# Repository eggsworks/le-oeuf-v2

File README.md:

## L'oeuf

An ultra-low profile (Kailh PG1316S) keyboard inspired by Le Chiffre.

## PCB

L'oeuf is a semi-integrated PCB using an E73 BLE module. It is intended to be fully SMT assembled.

A mid-mount USB-C port and JST ACH battery connector keep the board as thin as possible.

## Firmware

ZMK firmware available from [eggsworks/zmk-config](https://github.com/eggsworks/zmk-config/)

## License

This design is available under the terms of the [CERN-OHL-S](LICENSE).

## Acknowledgements

- Inspired by the original [tominabox1/Le-Chiffre-Keyboard](https://github.com/tominabox1/Le-Chiffre-Keyboard/)
- E73 supporting circuitry derived from [krikun98/Willis](https://github.com/krikun98/Willis)
- MCU footprint derived from [ebastler/marbastlib](https://github.com/ebastler/marbastlib/)
- Switch footprint derived from [mikeholscher/zmk-config-mikefive](https://github.com/mikeholscher/zmk-config-mikefive/)
- Layout derived from ergogen source supplied for [sporkus/le_capybara_keyboard](https://github.com/sporkus/le_capybara_keyboard)
- PCB art kindly provided by transthropology

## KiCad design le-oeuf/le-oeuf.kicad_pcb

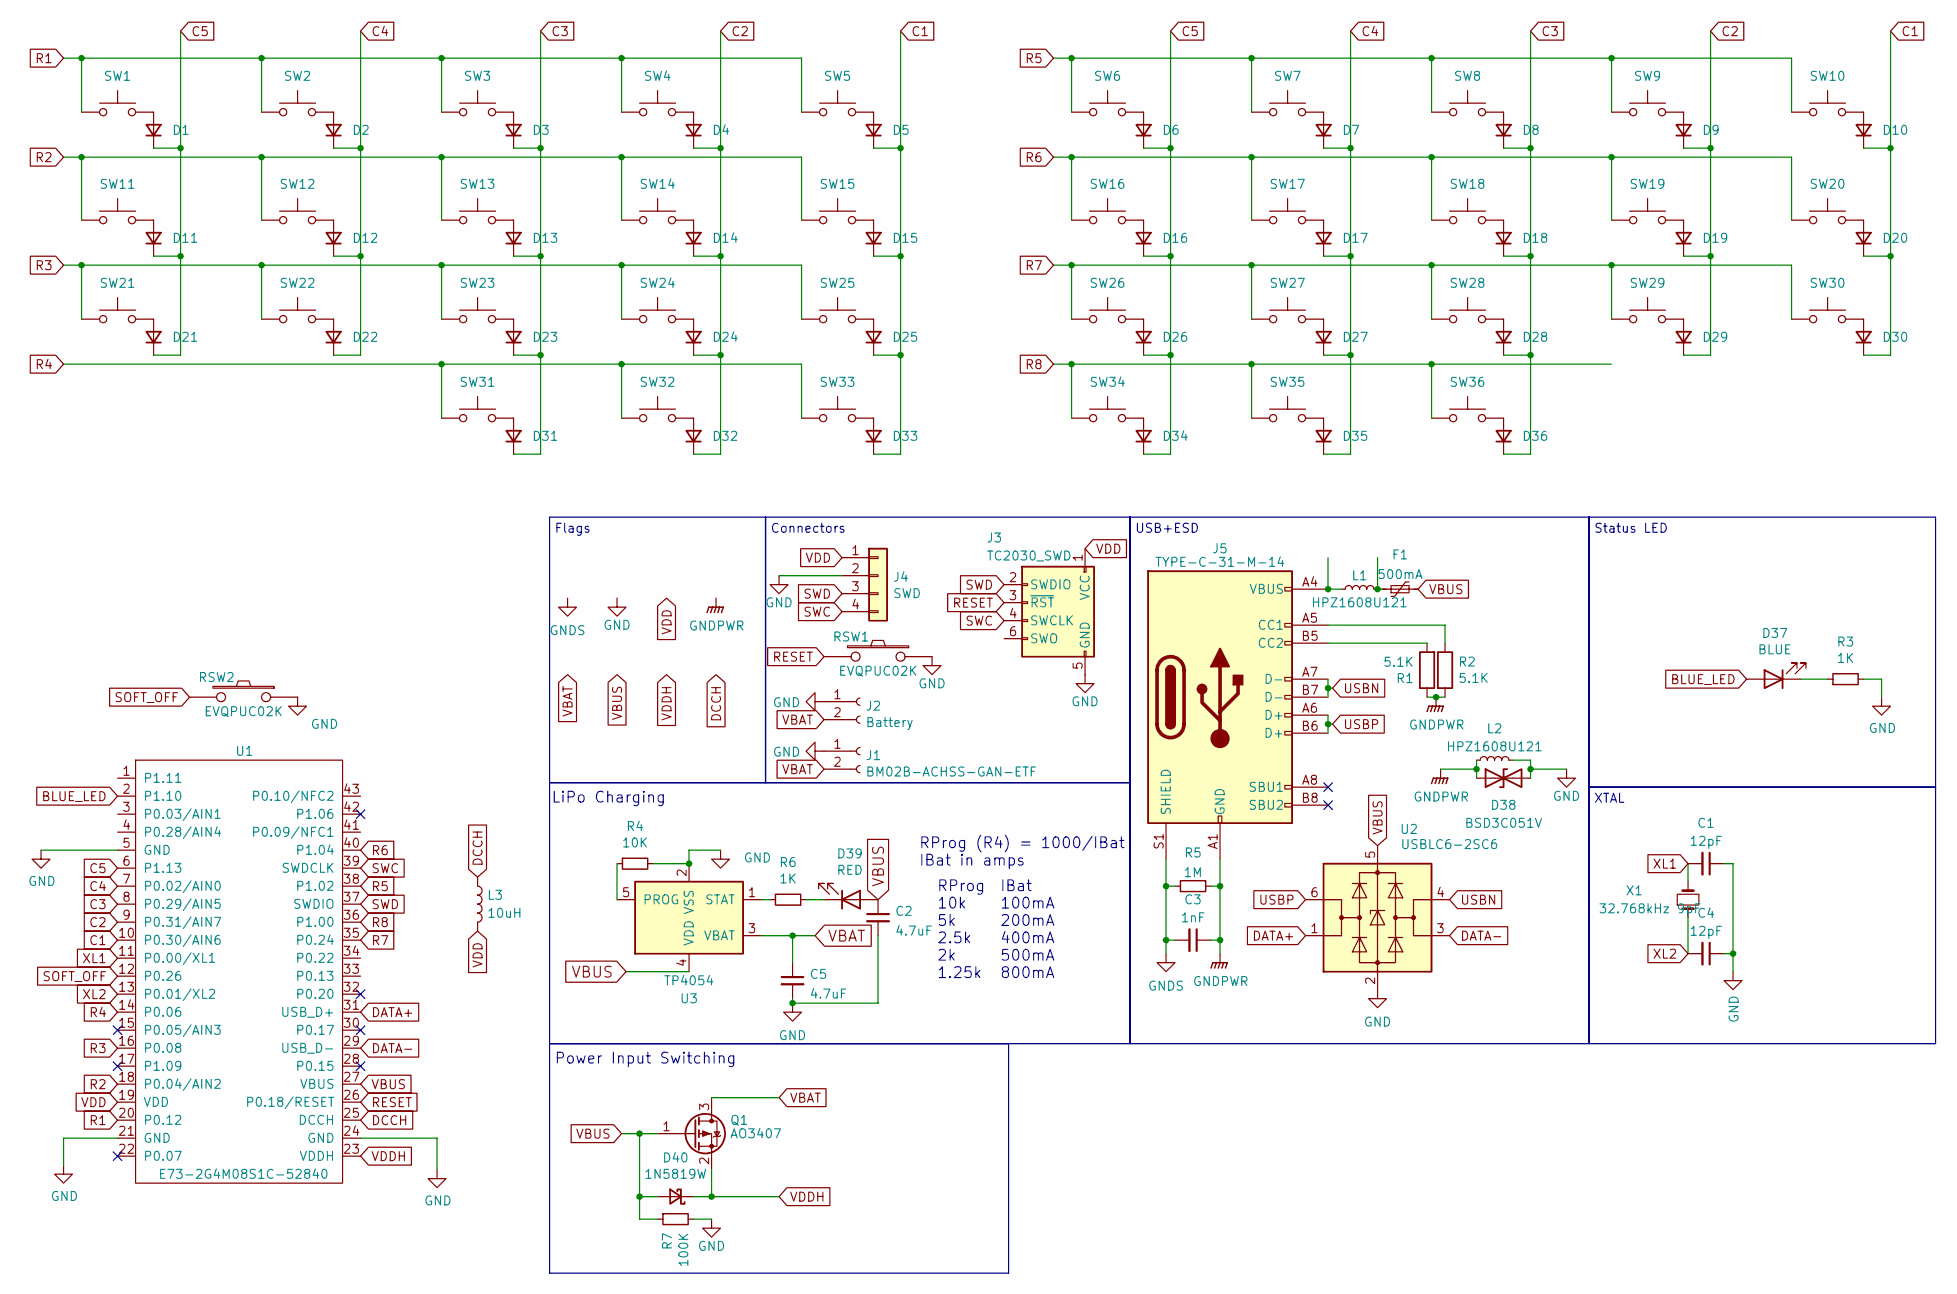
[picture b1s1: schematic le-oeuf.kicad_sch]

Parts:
C1, C4: 12pF; C_0603_1608Metric; MPN 0603CG120J500NT; LCSC C1642
C2, C5: 4.7uF; C_0603_1608Metric; MPN CL10A475KO8NNNC; LCSC C19666
C3: 1nF; C_0603_1608Metric; MPN CL10B102KB8NNNC; LCSC C1588
D1, D2, D3, D4, D5, D6, D7, D8, D9, D10, D11, D12, D13, D14, D15, D16, D17, D18, D19, D20, D21, D22, D23, D24, D25, D26, D27, D28, D29, D30, D31, D32, D33, D34, D35, D36, D40: 1N5819W; D_SOD-123; MPN 1N5819W; LCSC C727115
D37: BLUE; LED_1206_3216Metric; MPN XL-3216UBC; LCSC C965827
D38: BSD3C051V; D_SOD-323; MPN BSD3C051V; LCSC C151996
D39: RED; LED_1206_3216Metric; MPN XL-3216SURC; LCSC C965822
F1: 500mA; Fuse_1206_3216Metric; MPN BSMD1206-050-6V; LCSC C883122
J1: BM02B-ACHSS-GAN-ETF; JST_ACH_BM02B-ACHSS-GAN-ETF_1x02-1MP_P1.20mm_Vertical; MPN BM02B-ACHSS-GAN-ETF(LF)(SN); LCSC C5118738
J2: Battery; PinHeader_1x02_P2.00mm_Vertical
J3: TC2030_SWD; CON_TC2030_outlined
J4: SWD; PinHeader_1x04_P2.54mm_Vertical
J5: TYPE-C-31-M-14; USB_C_Receptacle_HRO_TYPE-C-31-M-14; MPN TYPE-C-31-M-14; LCSC C223907
L1, L2: HPZ1608U121; L_0603_1608Metric; MPN HPZ1608U121-2R0TF; LCSC C919153
L3: 10uH; L_0603_1608Metric; MPN MLF1608E100JT000; LCSC C275361
Q1: AO3407; SOT-23; MPN AO3407; LCSC C5148473
R1, R2: 5.1K; R_0603_1608Metric; MPN RC0603FR-075K1L; LCSC C105580
R3, R6: 1K; R_0603_1608Metric; MPN RC0603FR-071KL; LCSC C22548
R4: 10K; R_0603_1608Metric; MPN 0603WAF1002T5E; LCSC C25804
R5: 1M; R_0603_1608Metric; MPN 0603WAF1004T5E; LCSC C22935
R7: 100K; R_0603_1608Metric; MPN RC0603FR-07100KL; LCSC C14675
RSW1, RSW2: EVQPUC02K; Panasonic_EVQPUL_EVQPUC; MPN EVQPUC02K; LCSC C79174
SW1, SW2, SW3, SW4, SW5, SW6, SW7, SW8, SW9, SW10, SW11, SW12, SW13, SW14, SW15, SW16, SW17, SW18, SW19, SW20, SW21, SW22, SW23, SW24, SW25, SW26, SW27, SW28, SW29, SW30, SW31, SW32, SW33, SW34, SW35, SW36: PG1425; CPG1316S01D02_mikeholscher
U1: E73-2G4M08S1C-52840; nRF52840_E73-2G4M08S1C; MPN C356849; LCSC C356849
U2: USBLC6-2SC6; TSOT-23-6; MPN TPUSBLC6-2SC6; LCSC C558442
U3: TP4054; SOT-23-5; MPN TP4054; LCSC C5381776
X1: 32.768kHz 9pF; Crystal_SMD_MicroCrystal_CM9V-T1A-2Pin_1.6x1.0mm; MPN X161032768KLD2SI; LCSC C383846

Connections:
BLUE_LED: D37.2 (A), U1.2 (P1.10)
C1: D5.1 (K), D10.1 (K), D15.1 (K), D20.1 (K), D25.1 (K), D30.1 (K), D33.1 (K), U1.10 (P0.30/AIN6)
C2: D4.1 (K), D9.1 (K), D14.1 (K), D19.1 (K), D24.1 (K), D29.1 (K), D32.1 (K), U1.9 (P0.31/AIN7)
C3: D3.1 (K), D8.1 (K), D13.1 (K), D18.1 (K), D23.1 (K), D28.1 (K), D31.1 (K), D36.1 (K), U1.8 (P0.29/AIN5)
C4: D2.1 (K), D7.1 (K), D12.1 (K), D17.1 (K), D22.1 (K), D27.1 (K), D35.1 (K), U1.7 (P0.02/AIN0)
C5: D1.1 (K), D6.1 (K), D11.1 (K), D16.1 (K), D21.1 (K), D26.1 (K), D34.1 (K), U1.6 (P1.13)
DATA+: U1.31 (USB_D+), U2.1 (I/O1)
DATA-: U1.29 (USB_D-), U2.3 (I/O2)
DCCH: L3.1, U1.25 (DCCH)
GND: C1.1, C2.2, C4.1, C5.2, D38.2 (A2), J1.1, J2.1, J3.5 (GND), J4.2, L2.2, R3.2, R4.2, R7.2, RSW1.1, RSW2.1, U1.5 (GND), U1.21 (GND), U1.24 (GND), U2.2 (GND), U3.2 (VSS)
GNDPWR: C3.1, D38.1 (A1), J5.A1 (GND), J5.A12 (GND), J5.B1 (GND), J5.B12 (GND), L2.1, R1.1, R2.2, R5.2
GNDS: C3.2, J5.S1 (SHIELD), R5.1
unnamed: D1.2 (A), SW1.2
unnamed: D2.2 (A), SW2.2
unnamed: D3.2 (A), SW3.2
unnamed: D4.2 (A), SW4.2
unnamed: D5.2 (A), SW5.2
unnamed: D6.2 (A), SW6.2
unnamed: D7.2 (A), SW7.2
unnamed: D8.2 (A), SW8.2
unnamed: D9.2 (A), SW9.2
unnamed: D10.2 (A), SW10.2
unnamed: D11.2 (A), SW11.2
unnamed: D12.2 (A), SW12.2
unnamed: D13.2 (A), SW13.2
unnamed: D14.2 (A), SW14.2
unnamed: D15.2 (A), SW15.2
unnamed: D16.2 (A), SW16.2
unnamed: D17.2 (A), SW17.2
unnamed: D18.2 (A), SW18.2
unnamed: D19.2 (A), SW19.2
unnamed: D20.2 (A), SW20.2
unnamed: D21.2 (A), SW21.2
unnamed: D22.2 (A), SW22.2
unnamed: D23.2 (A), SW23.2
unnamed: D24.2 (A), SW24.2
unnamed: D25.2 (A), SW25.2
unnamed: D26.2 (A), SW26.2
unnamed: D27.2 (A), SW27.2
unnamed: D28.2 (A), SW28.2
unnamed: D29.2 (A), SW29.2
unnamed: D30.2 (A), SW30.2
unnamed: D31.2 (A), SW31.2
unnamed: D32.2 (A), SW32.2
unnamed: D33.2 (A), SW33.2
unnamed 45: D34.2 (A), SW34.2; also elsewhere on the board
unnamed: D35.2 (A), SW35.2
unnamed: D36.2 (A), SW36.2
unnamed: D37.1 (K), R3.1
unnamed: D39.1 (K), R6.1
unnamed: F1.1, L1.2
unnamed: J5.A5 (CC1), R2.1
unnamed: J5.B5 (CC2), R1.2
unnamed: J5.A4 (VBUS), J5.A9 (VBUS), J5.B4 (VBUS), J5.B9 (VBUS), L1.1
unnamed: R4.1, U3.5 (PROG)
unnamed: R6.2, U3.1 (STAT)
R1: SW1.1, SW2.1, SW3.1, SW4.1, SW5.1, U1.20 (P0.12)
R2: SW11.1, SW12.1, SW13.1, SW14.1, SW15.1, U1.18 (P0.04/AIN2)
R3: SW21.1, SW22.1, SW23.1, SW24.1, SW25.1, U1.16 (P0.08)
R4: SW31.1, SW32.1, SW33.1, U1.14 (P0.06)
R5: SW6.1, SW7.1, SW8.1, SW9.1, SW10.1, U1.38 (P1.02)
R6: SW16.1, SW17.1, SW18.1, SW19.1, SW20.1, U1.40 (P1.04)
R7: SW26.1, SW27.1, SW28.1, SW29.1, SW30.1, U1.35 (P0.24)
R8: SW34.1, SW35.1, SW36.1, U1.36 (P1.00); also elsewhere on the board
RESET: J3.3 (~RST), RSW1.2, U1.26 (P0.18/RESET)
SOFT_OFF: RSW2.2, U1.12 (P0.26)
SWC: J3.4 (SWCLK), J4.4, U1.39 (SWDCLK)
SWD: J3.2 (SWDIO), J4.3, U1.37 (SWDIO)
USBN: J5.A7 (D-), J5.B7 (D-), U2.4 (I/O2)
USBP: J5.A6 (D+), J5.B6 (D+), U2.6 (I/O1)
VBAT: C5.1, J1.2, J2.2, Q1.3 (D), U3.3 (VBAT)
VBUS: C2.1, D39.2 (A), D40.2 (A), F1.2, Q1.1 (G), R7.1, U1.27 (VBUS), U2.5 (VBUS), U3.4 (VDD)
VDD: J3.1 (VCC), J4.1, L3.2, U1.19 (VDD)
VDDH: D40.1 (K), Q1.2 (S), U1.23 (VDDH)
XL1: C1.2, U1.11 (P0.00/XL1), X1.2
XL2: C4.2, U1.13 (P0.01/XL2), X1.1

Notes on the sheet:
RProg 10k 5k 2.5k 2k 1.25k
Connectors
LiPo Charging
Power Input Switching
XTAL
IBat 100mA 200mA 400mA 500mA 800mA
Flags
Status LED
USB+ESD
RProg (R4) = 1000/IBat IBat in amps

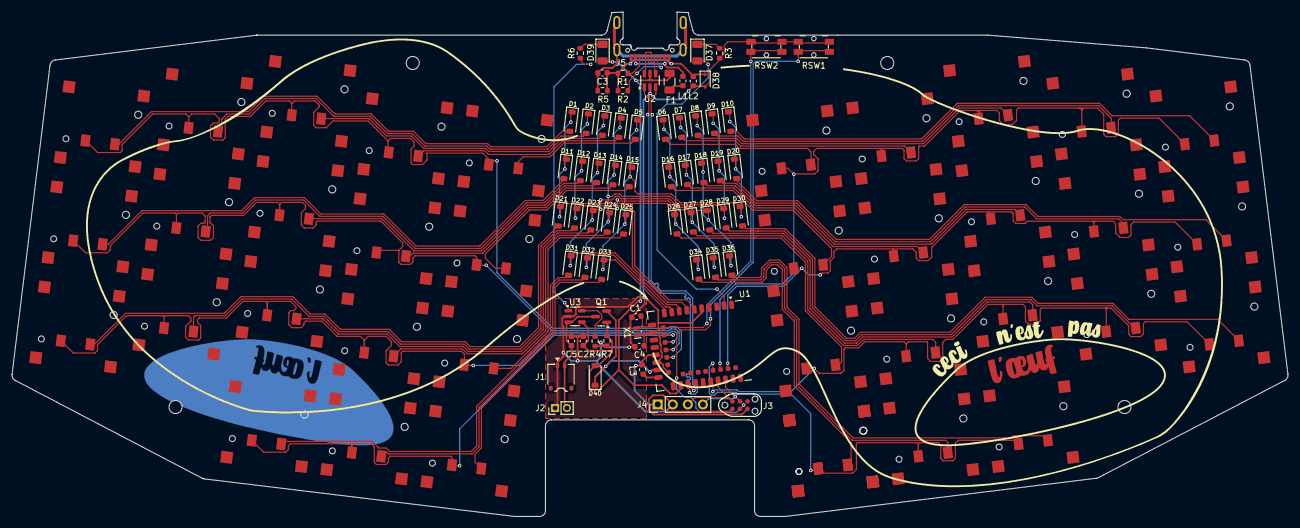
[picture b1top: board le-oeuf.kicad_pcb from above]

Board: 2 copper layers, 215.1 x 85.0 mm, 105 parts (0 on the bottom side), 76 nets.

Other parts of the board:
SW34#2: PG1425; CPG1316S01D02_mikeholscher

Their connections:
unnamed 45: SW34#2.2; also elsewhere on the board
R8: SW34#2.1; also elsewhere on the board

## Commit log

2024-11-13 oops, move license and readme files to repo root
2024-11-21 prepare for publication
2024-11-21 Readme formatting
2024-11-21 Fix quantity typo
2024-11-23 Add case and update readme
2024-11-26 do not push this commit
2024-12-01 finish routing
2024-12-12 import art
2024-12-18 prototype ordered
2024-12-20 bom updates
2025-05-14 Cleanup for v2 push
2025-05-14 Add switch footprint
2025-05-14 Remove PG1425 footprint
2025-05-14 Remove xiao footprint
2025-05-14 Add images

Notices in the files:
le-oeuf/le-oeuf.kicad_pcb:
© 2024 Travis Mick
CERN-OHL-S-2.0
